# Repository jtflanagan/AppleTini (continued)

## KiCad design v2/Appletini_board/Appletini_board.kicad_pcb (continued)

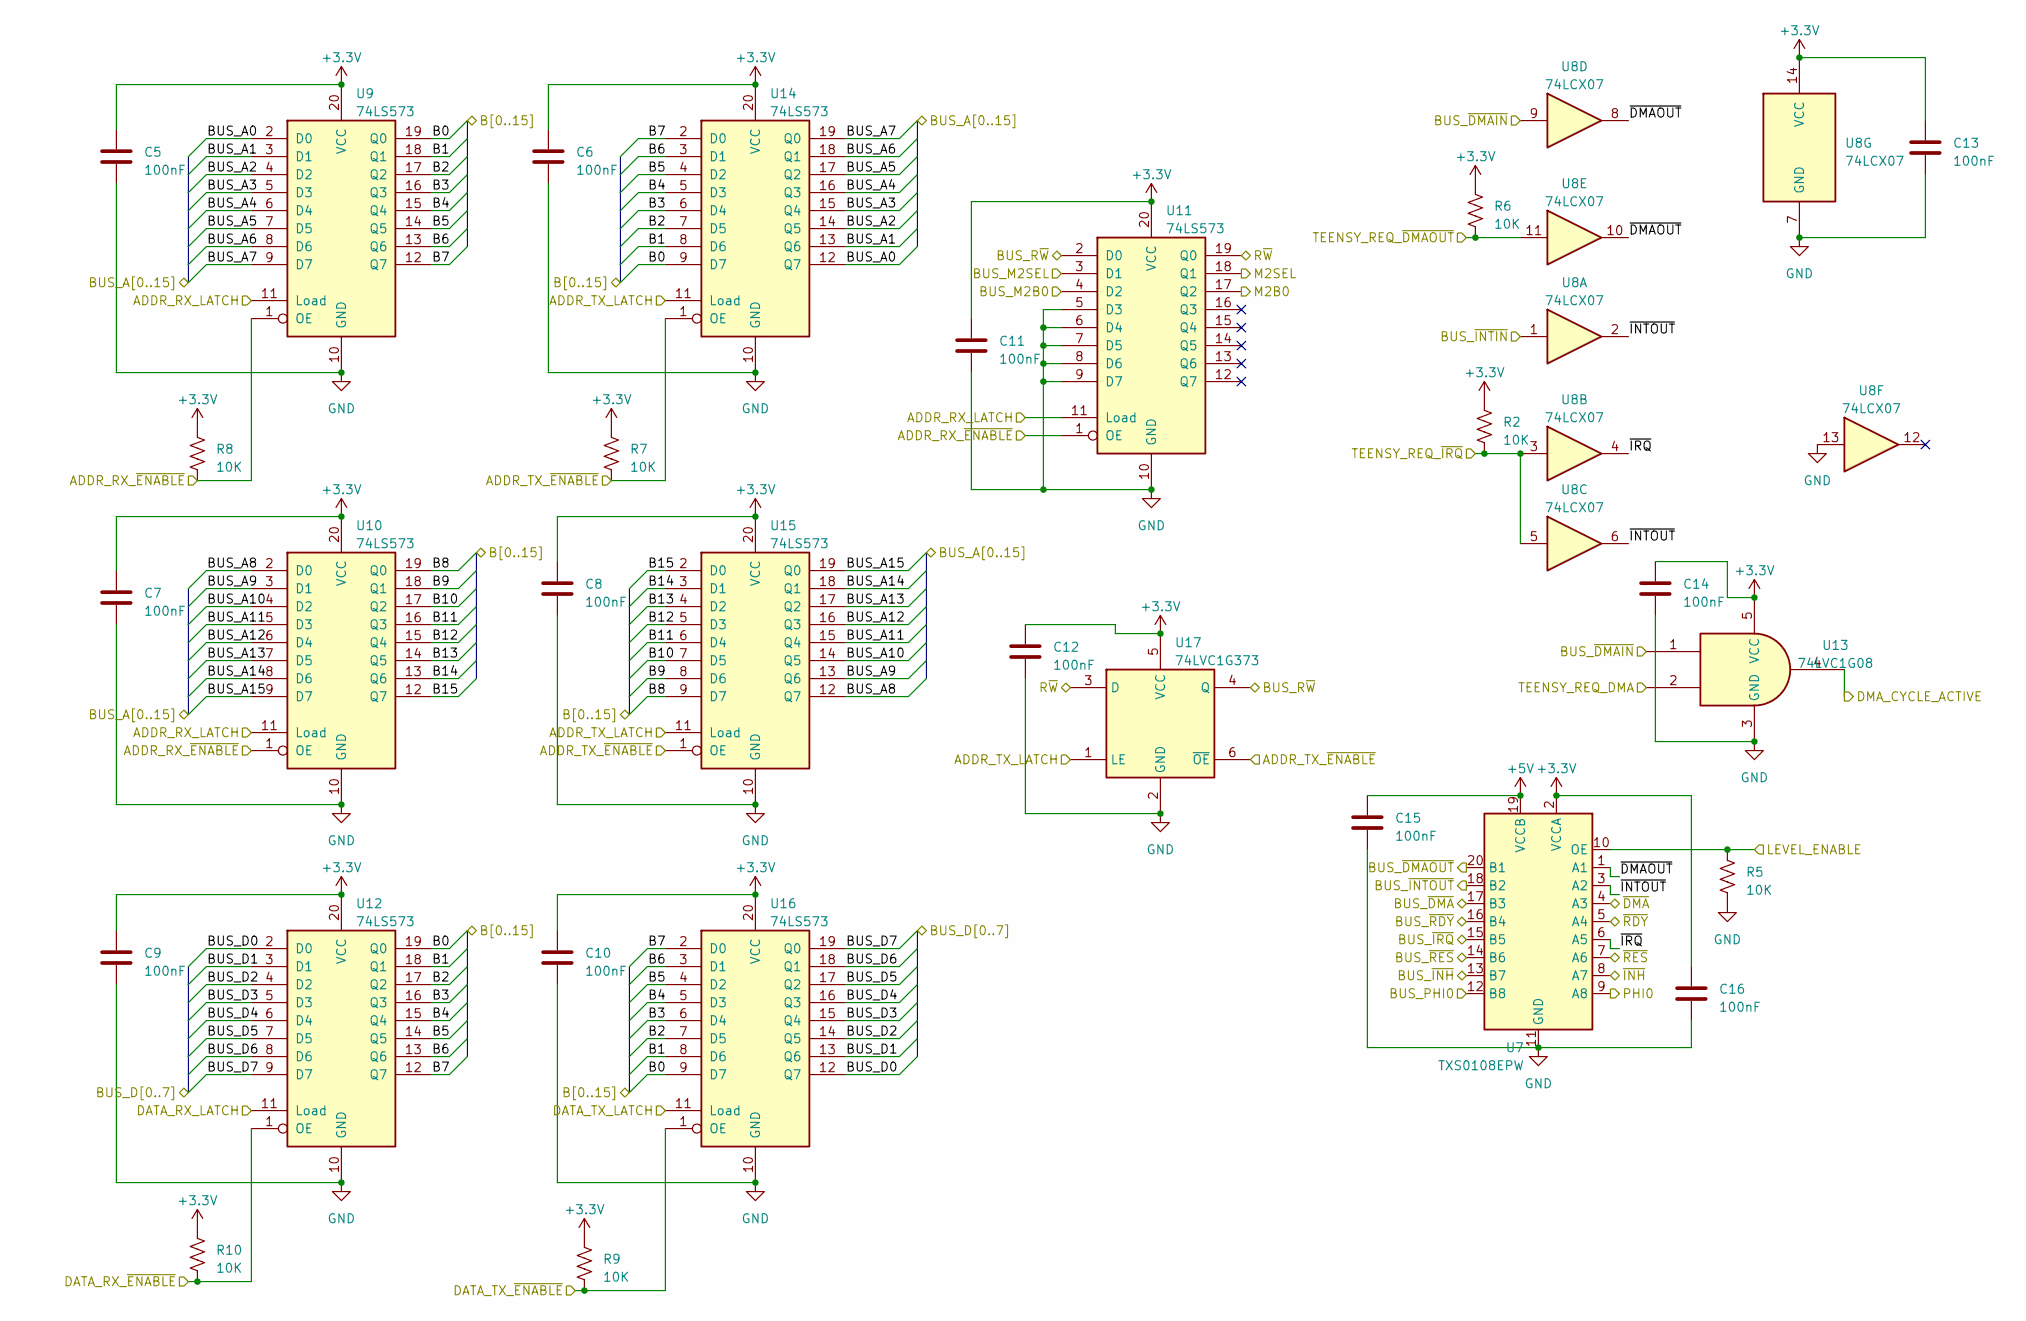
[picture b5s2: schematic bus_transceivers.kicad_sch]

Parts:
C5, C6, C7, C8, C9, C10, C11, C12: 100nF; C_1206_3216Metric
C13, C14, C15, C16: 100nF; C_1206_3216Metric; LCSC C24497
R2, R6, R7, R8, R9, R10: 10K; R_0402_1005Metric; LCSC C2991755
R5: 10K; R_0402_1005Metric
U7: TXS0108EPW; TSSOP-20_4.4x6.5mm_P0.65mm; LCSC C17206
U8: 74LCX07; TSSOP-14_4.4x5mm_P0.65mm; LCSC C7809
U9: 74LS573; TSSOP-20_4.4x6.5mm_P0.65mm; LCSC C113280
U10, U11, U12, U14, U15, U16: 74LS573; TSSOP-20_4.4x6.5mm_P0.65mm
U13: 74LVC1G08; SOT-23-5; LCSC C7666
U17: 74LVC1G373; SOT-23-6; LCSC C128413

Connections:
+3.3V: C5.1, C6.1, C7.1, C8.1, C9.1, C10.1, C11.1, C12.1, C13.1, C14.1, C16.1, R2.1, R6.1, R7.1, R8.1, R9.1, R10.1, U7.2 (VCCA), U8.14 (VCC), U9.20 (VCC), U10.20 (VCC), U11.20 (VCC), U12.20 (VCC), U13.5 (VCC), U14.20 (VCC), U15.20 (VCC), U16.20 (VCC), U17.5 (VCC); also elsewhere on the board
+5V: C15.1, U7.19 (VCCB); also elsewhere on the board
/ADDR_RX_LATCH: U9.11 (Load), U10.11 (Load), U11.11 (Load); also elsewhere on the board
/ADDR_RX_~ENABLE: R8.2, U9.1 (OE), U10.1 (OE), U11.1 (OE); also elsewhere on the board
/ADDR_TX_LATCH: U14.11 (Load), U15.11 (Load), U17.1 (LE); also elsewhere on the board
/ADDR_TX_~ENABLE: R7.2, U14.1 (OE), U15.1 (OE), U17.6 (~OE); also elsewhere on the board
/B0: U9.19 (Q0), U12.19 (Q0), U14.9 (D7), U16.9 (D7); also elsewhere on the board
/B1: U9.18 (Q1), U12.18 (Q1), U14.8 (D6), U16.8 (D6); also elsewhere on the board
/B2: U9.17 (Q2), U12.17 (Q2), U14.7 (D5), U16.7 (D5); also elsewhere on the board
/B3: U9.16 (Q3), U12.16 (Q3), U14.6 (D4), U16.6 (D4); also elsewhere on the board
/B4: U9.15 (Q4), U12.15 (Q4), U14.5 (D3), U16.5 (D3); also elsewhere on the board
/B5: U9.14 (Q5), U12.14 (Q5), U14.4 (D2), U16.4 (D2); also elsewhere on the board
/B6: U9.13 (Q6), U12.13 (Q6), U14.3 (D1), U16.3 (D1); also elsewhere on the board
/B7: U9.12 (Q7), U12.12 (Q7), U14.2 (D0), U16.2 (D0); also elsewhere on the board
/B8: U10.19 (Q0), U15.9 (D7); also elsewhere on the board
/B9: U10.18 (Q1), U15.8 (D6); also elsewhere on the board
/B10: U10.17 (Q2), U15.7 (D5); also elsewhere on the board
/B11: U10.16 (Q3), U15.6 (D4); also elsewhere on the board
/B12: U10.15 (Q4), U15.5 (D3); also elsewhere on the board
/B13: U10.14 (Q5), U15.4 (D2); also elsewhere on the board
/B14: U10.13 (Q6), U15.3 (D1); also elsewhere on the board
/B15: U10.12 (Q7), U15.2 (D0); also elsewhere on the board
/BUS_A0: U9.2 (D0), U14.12 (Q7); also elsewhere on the board
/BUS_A1: U9.3 (D1), U14.13 (Q6); also elsewhere on the board
/BUS_A2: U9.4 (D2), U14.14 (Q5); also elsewhere on the board
/BUS_A3: U9.5 (D3), U14.15 (Q4); also elsewhere on the board
/BUS_A4: U9.6 (D4), U14.16 (Q3); also elsewhere on the board
/BUS_A5: U9.7 (D5), U14.17 (Q2); also elsewhere on the board
/BUS_A6: U9.8 (D6), U14.18 (Q1); also elsewhere on the board
/BUS_A7: U9.9 (D7), U14.19 (Q0); also elsewhere on the board
/BUS_A8: U10.2 (D0), U15.12 (Q7); also elsewhere on the board
/BUS_A9: U10.3 (D1), U15.13 (Q6); also elsewhere on the board
/BUS_A10: U10.4 (D2), U15.14 (Q5); also elsewhere on the board
/BUS_A11: U10.5 (D3), U15.15 (Q4); also elsewhere on the board
/BUS_A12: U10.6 (D4), U15.16 (Q3); also elsewhere on the board
/BUS_A13: U10.7 (D5), U15.17 (Q2); also elsewhere on the board
/BUS_A14: U10.8 (D6), U15.18 (Q1); also elsewhere on the board
/BUS_A15: U10.9 (D7), U15.19 (Q0); also elsewhere on the board
/BUS_D0: U12.2 (D0), U16.12 (Q7); also elsewhere on the board
/BUS_D1: U12.3 (D1), U16.13 (Q6); also elsewhere on the board
/BUS_D2: U12.4 (D2), U16.14 (Q5); also elsewhere on the board
/BUS_D3: U12.5 (D3), U16.15 (Q4); also elsewhere on the board
/BUS_D4: U12.6 (D4), U16.16 (Q3); also elsewhere on the board
/BUS_D5: U12.7 (D5), U16.17 (Q2); also elsewhere on the board
/BUS_D6: U12.8 (D6), U16.18 (Q1); also elsewhere on the board
/BUS_D7: U12.9 (D7), U16.19 (Q0); also elsewhere on the board
/BUS_M2B0: U11.4 (D2); also elsewhere on the board
/BUS_M2SEL: U11.3 (D1); also elsewhere on the board
/BUS_PHI0: U7.12 (B8); also elsewhere on the board
/BUS_R~W: U11.2 (D0), U17.4 (Q); also elsewhere on the board
/BUS_~DMAIN: U8.9, U13.1; also elsewhere on the board
/BUS_~DMAOUT: U7.20 (B1); also elsewhere on the board
/BUS_~DMA: U7.17 (B3); also elsewhere on the board
/BUS_~INH: U7.13 (B7); also elsewhere on the board
/BUS_~INTIN: U8.1; also elsewhere on the board
/BUS_~INTOUT: U7.18 (B2); also elsewhere on the board
/BUS_~IRQ: U7.15 (B5); also elsewhere on the board
/BUS_~RDY: U7.16 (B4); also elsewhere on the board
/BUS_~RES: U7.14 (B6); also elsewhere on the board
/Bus transceivers/~DMAOUT: U7.1 (A1), U8.8, U8.10
/Bus transceivers/~INTOUT: U7.3 (A2), U8.2, U8.6
/Bus transceivers/~IRQ: U7.6 (A5), U8.4
/DATA_RX_LATCH: U12.11 (Load); also elsewhere on the board
/DATA_RX_~ENABLE: R10.2, U12.1 (OE); also elsewhere on the board
/DATA_TX_LATCH: U16.11 (Load); also elsewhere on the board
/DATA_TX_~ENABLE: R9.2, U16.1 (OE); also elsewhere on the board
/DMA_CYCLE_ACTIVE: U13.4; also elsewhere on the board
/LEVEL_ENABLE: R5.1, U7.10 (OE); also elsewhere on the board
/M2B0: U11.17 (Q2); also elsewhere on the board
/M2SEL: U11.18 (Q1); also elsewhere on the board
/PHI0: U7.9 (A8); also elsewhere on the board
/R~W: U11.19 (Q0), U17.3 (D); also elsewhere on the board
/TEENSY_REQ_DMA: U13.2; also elsewhere on the board
/TEENSY_REQ_~DMAOUT: R6.2, U8.11; also elsewhere on the board
/TEENSY_REQ_~IRQ: R2.2, U8.3, U8.5; also elsewhere on the board
/~DMA: U7.4 (A3); also elsewhere on the board
/~INH: U7.8 (A7); also elsewhere on the board
/~RDY: U7.5 (A4); also elsewhere on the board
/~RES: U7.7 (A6); also elsewhere on the board
GND: C5.2, C6.2, C7.2, C8.2, C9.2, C10.2, C11.2, C12.2, C13.2, C14.2, C15.2, C16.2, R5.2, U7.11 (GND), U8.7 (GND), U8.13, U9.10 (GND), U10.10 (GND), U11.5 (D3), U11.6 (D4), U11.7 (D5), U11.8 (D6), U11.9 (D7), U11.10 (GND), U12.10 (GND), U13.3 (GND), U14.10 (GND), U15.10 (GND), U16.10 (GND), U17.2 (GND); also elsewhere on the board

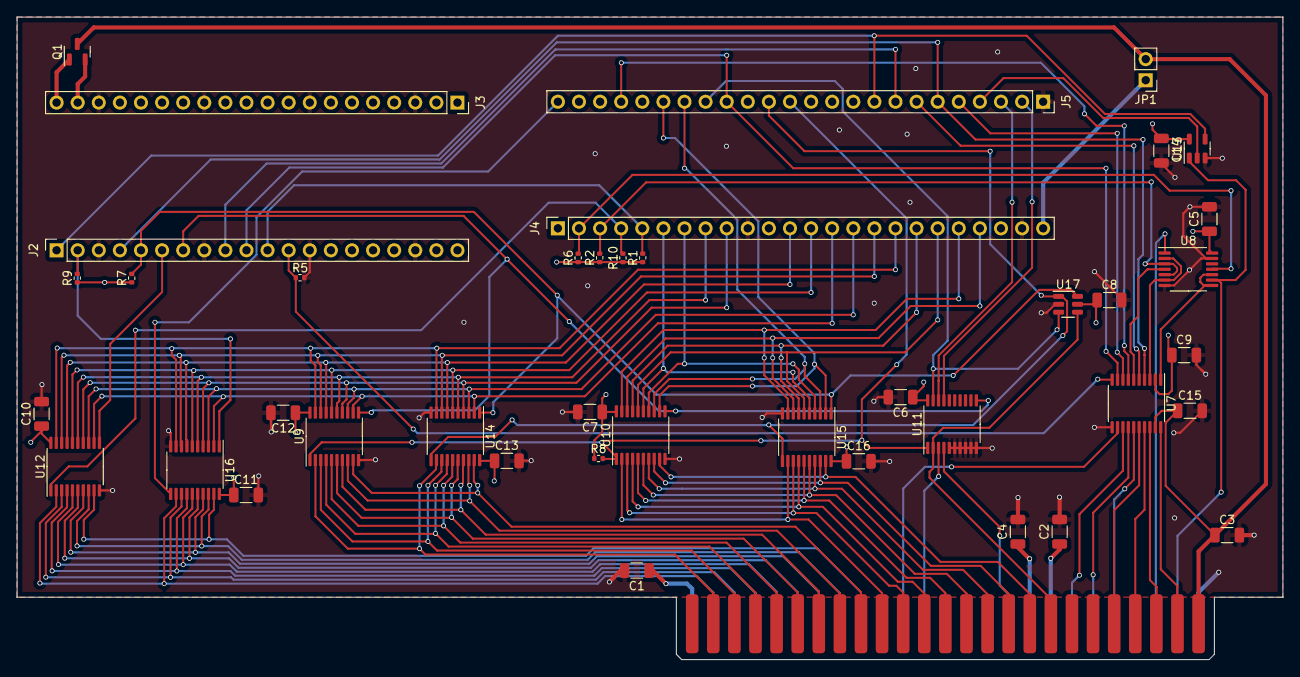
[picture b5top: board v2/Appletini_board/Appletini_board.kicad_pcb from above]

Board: 4 copper layers, 152.4 x 77.4 mm, 42 parts (0 on the bottom side), 88 nets.

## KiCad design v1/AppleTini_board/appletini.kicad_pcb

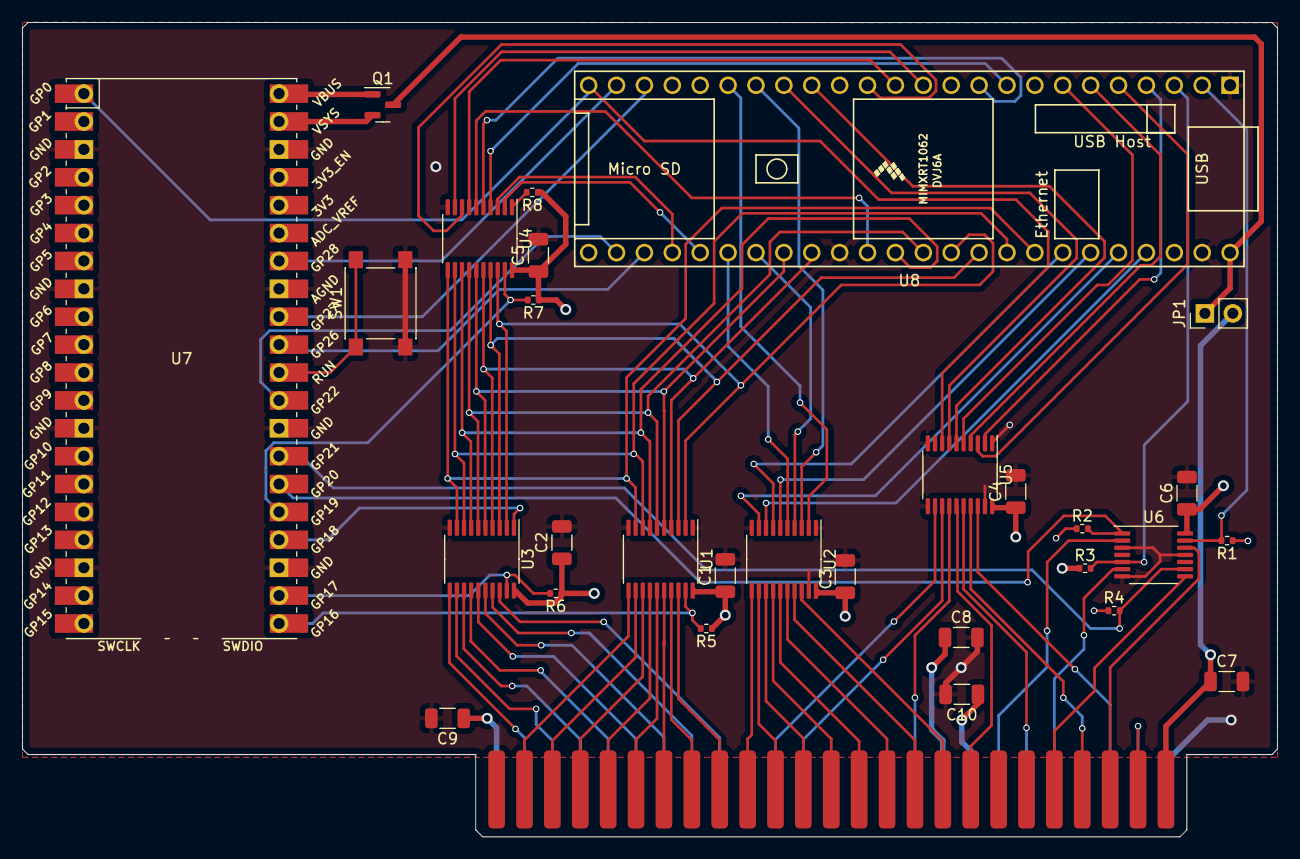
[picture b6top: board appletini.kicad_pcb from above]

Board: 4 copper layers, 114.3 x 74.2 mm, 30 parts (0 on the bottom side), 90 nets.

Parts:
C1, C2, C3, C4, C5, C6, C7, C8, C9, C10: 0.1uF; C_1206_3216Metric
J1: Conn_02x25_Counter_Clockwise; AppleIIBus_Edge
JP1: Jumper_2_Open; PinHeader_1x02_P2.54mm_Vertical
Q1: DMG2305UX-7; SOT-23
R1, R2, R3, R4, R5, R6, R7, R8: 10K; R_0402_1005Metric
SW1: SW_Push; SW_Push_1P1T_NO_6x6mm_H9.5mm
U1, U2, U3, U4, U5: 74LS245; TSSOP-20_4.4x6.5mm_P0.65mm
U6: 74LS07; TSSOP-14_4.4x5mm_P0.65mm
U7: Pico; RPi_Pico_SMD_TH
U8: Teensy4.1; Teensy41

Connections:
+3.3V: C1.1, C2.1, C3.1, C4.1, C5.1, C6.1, R1.1, R2.1, R3.1, R4.1, R5.1, R6.1, R7.1, R8.1, U1.20 (VCC), U2.20 (VCC), U3.20 (VCC), U4.20 (VCC), U5.20 (VCC), U6.14 (VCC), U8.46 (3V3)
+5V: C7.1, J1.25, JP1.2 (B)
+12V: C9.1, J1.50
-5V: C8.1, J1.34
-12V: C10.1, J1.33
/ALO_EN: R5.2, U1.19 (CE), U7.21 (GPIO16)
/BUS_A0: J1.2, U1.11 (B7)
/BUS_A1: J1.3, U1.12 (B6)
/BUS_A2: J1.4, U1.13 (B5)
/BUS_A3: J1.5, U1.14 (B4)
/BUS_A4: J1.6, U1.15 (B3)
/BUS_A5: J1.7, U1.16 (B2)
/BUS_A6: J1.8, U1.17 (B1)
/BUS_A7: J1.9, U1.18 (B0)
/BUS_A8: J1.10, U2.11 (B7)
/BUS_A9: J1.11, U2.12 (B6)
/BUS_A10: J1.12, U2.13 (B5)
/BUS_A11: J1.13, U2.14 (B4)
/BUS_A12: J1.14, U2.15 (B3)
/BUS_A13: J1.15, U2.16 (B2)
/BUS_A14: J1.16, U2.17 (B1)
/BUS_A15: J1.17, U2.18 (B0)
/BUS_D0: J1.49, U3.11 (B7)
/BUS_D1: J1.48, U3.12 (B6)
/BUS_D2: J1.47, U3.13 (B5)
/BUS_D3: J1.46, U3.14 (B4)
/BUS_D4: J1.45, U3.15 (B3)
/BUS_D5: J1.44, U3.16 (B2)
/BUS_D6: J1.43, U3.17 (B1)
/BUS_D7: J1.42, U3.18 (B0)
/BUS_DMA: J1.22, U5.17 (B1)
/BUS_DMAPASS: J1.24, J1.27
/BUS_INH: J1.32, U6.2
/BUS_INTIN: J1.28, U5.18 (B0)
/BUS_INTOUT: J1.23, U6.12
/BUS_IRQ: J1.30, U6.6
/BUS_M2B0: J1.35, U5.14 (B4)
/BUS_PHI0: J1.40, U5.12 (B6)
/BUS_RDY: J1.21, U6.8
/BUS_RES: J1.31, U5.16 (B2)
/BUS_RW: J1.18, U5.15 (B3)
/BUS_uSYNC: J1.39, U5.13 (B5)
/DMA: U5.3 (A1), U8.5 (3_LRCLK2)
/D_DIR: U3.1 (A->B), U7.24 (GPIO18)
/D_EN: R6.2, U3.19 (CE), U7.22 (GPIO17)
/INH: R2.2, U6.1, U7.26 (GPIO20)
/INH_REQ: U7.29 (GPIO22), U8.26 (34_RX8)
/INTIN: U5.2 (A0), U8.4 (2_OUT2)
/INTOUT: R1.2, U6.13, U8.2 (0_RX1_CRX2_CS1)
/IRQ: R3.2, U6.5, U8.3 (1_TX1_CTX2_MISO1)
/M2B0: U5.6 (A4), U8.16 (24_A10_TX6_SCL2)
/OUT_D_EN: R7.2, U4.19 (CE), U7.25 (GPIO19)
/OUT_D_REQ: U7.34 (GPIO28_ADC2), U8.23 (31_CTX3)
/PHI0: U5.8 (A6), U7.1 (GPIO0), U8.24 (32_OUT1B)
/RDY: R4.2, U6.9, U7.27 (GPIO21)
/RDY_REQ: U7.31 (GPIO26_ADC0), U8.27 (35_TX8)
/RES: U5.4 (A2), U8.6 (4_BCLK2)
/RW: U5.5 (A3), U8.7 (5_IN2)
/TEENSY_IRQ: U7.32 (GPIO27_ADC1), U8.22 (30_CRX3)
/Transceivers/AHI0: U2.9 (A7), U8.44 (22_A8_CTX1)
/Transceivers/AHI1: U2.8 (A6), U8.45 (23_A9_CRX1_MCLK1)
/Transceivers/AHI2: U2.7 (A5), U8.42 (20_A6_TX5_LRCLK1)
/Transceivers/AHI3: U2.6 (A4), U8.43 (21_A7_RX5_BCLK1)
/Transceivers/AHI4: U2.5 (A3), U8.30 (38_CS1_IN1)
/Transceivers/AHI5: U2.4 (A2), U8.31 (39_MISO1_OUT1A)
/Transceivers/AHI6: U2.3 (A1), U8.18 (26_A12_MOSI1)
/Transceivers/AHI7: U2.2 (A0), U8.19 (27_A13_SCK1)
/Transceivers/ALO_D0: U1.9 (A7), U3.9 (A7), U4.11 (B7), U8.41 (19_A5_SCL)
/Transceivers/ALO_D1: U1.8 (A6), U3.8 (A6), U4.12 (B6), U8.40 (18_A4_SDA)
/Transceivers/ALO_D2: U1.7 (A5), U3.7 (A5), U4.13 (B5), U8.36 (14_A0_TX3_SPDIF_OUT)
/Transceivers/ALO_D3: U1.6 (A4), U3.6 (A4), U4.14 (B4), U8.37 (15_A1_RX3_SPDIF_IN)
/Transceivers/ALO_D4: U1.5 (A3), U3.5 (A3), U4.15 (B3), U8.32 (40_A16)
/Transceivers/ALO_D5: U1.4 (A2), U3.4 (A2), U4.16 (B2), U8.33 (41_A17)
/Transceivers/ALO_D6: U1.3 (A1), U3.3 (A1), U4.17 (B1), U8.39 (17_A3_TX4_SDA1)
/Transceivers/ALO_D7: U1.2 (A0), U3.2 (A0), U4.18 (B0), U8.38 (16_A2_RX4_SCL1)
/Transceivers/OUT_D0: U4.9 (A7), U8.12 (10_CS_MQSR)
/Transceivers/OUT_D1: U4.8 (A6), U8.14 (12_MISO_MQSL)
/Transceivers/OUT_D2: U4.7 (A5), U8.13 (11_MOSI_CTX1)
/Transceivers/OUT_D3: U4.6 (A4), U8.35 (13_SCK_LED)
/Transceivers/OUT_D4: U4.5 (A3), U8.10 (8_TX2_IN1)
/Transceivers/OUT_D5: U4.4 (A2), U8.9 (7_RX2_OUT1A)
/Transceivers/OUT_D6: U4.3 (A1), U8.28 (36_CS)
/Transceivers/OUT_D7: U4.2 (A0), U8.29 (37_CS)
/VBUS: Q1.1 (G), U7.40 (VBUS)
/VIN: JP1.1 (A), Q1.3 (D), U8.48 (VIN)
/VSYS: Q1.2 (S), U7.39 (VSYS)
/uSYNC: U5.7 (A5), U8.17 (25_A11_RX6_SDA2)
GND: C1.2, C2.2, C3.2, C4.2, C5.2, C6.2, C7.2, C8.2, C9.2, C10.2, J1.26, SW1.2, U1.1 (A->B), U1.10 (GND), U2.1 (A->B), U2.10 (GND), U2.19 (CE), U3.10 (GND), U4.10 (GND), U5.1 (A->B), U5.10 (GND), U5.11 (B7), U5.19 (CE), U6.3, U6.7 (GND), U6.11, U7.3 (GND), U7.8 (GND), U7.13 (GND), U7.18 (GND), U7.23 (GND), U7.28 (GND), U7.33 (AGND), U7.38 (GND), U8.1 (GND), U8.34 (GND), U8.47 (GND)
unnamed: R8.2, U4.1 (A->B)
unnamed: SW1.1, U7.30 (RUN)

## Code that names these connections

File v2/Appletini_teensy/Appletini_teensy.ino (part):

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  bus_address = (addr_port6_pins & 0xffff0000) >> 16;
  // these are set to the offsets they will eventually get used as
  // for event publish, and used in boolean context otherwise
  bus_rw = (addr_port6_pins & (1 << 13)) ? (1 << 24) : 0;
  bus_m2sel = (addr_port6_pins & (1 << 2)) ? (1 << 25) : 0;
  bus_m2b0 = (addr_port6_pins & (1 << 3)) ? (1 << 26) : 0;
  bus_reset = (port9_pins & (1 << 31)) ? (1 << 27) : 0;

  // make whatever decision as to what to do on this bus cycle based on
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  pinMode(PIN_RW, INPUT);

  // M2SEL on IIgs, uSYNC on IIe.  Always an input.
  pinMode(PIN_M2SEL, INPUT);
  // M2B0 on IIgs, not used on IIe. Always an input.
  pinMode(PIN_M2B0, INPUT);

  // ADDR_RX_ENABLE
  // DATA_RX_ENABLE
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  // the bus interrupt can snap the address lines immediately.
  // other bus actions will deassert ADDR_RX_ENABLE but we return
  // to a default state of ADDR_RX_ENABLE afterward.
  init_output_pin(PIN_ADDR_RX_ENABLE, LOW);
  init_output_pin(PIN_DATA_RX_ENABLE, HIGH);

  // ADDR_TX_LATCH
  // DATA_TX_LATCH
  // pins to tell the TX latches to retain their latched values.
  // Always outputs, init low
  init_output_pin(PIN_ADDR_TX_LATCH, LOW);
  init_output_pin(PIN_DATA_TX_LATCH, LOW);

  // TEENSY_EMIT_DATA
  // pin to tell Pico that the current bus cycle should emit the latched data byte.
  // always outputs, init high
  init_output_pin(PIN_TEENSY_EMIT_DATA, HIGH);

  // TEENSY_REQ_DMAOUT
  // pin to pre-request DMA.  This should be asserted the cycle before beginning DMA request.
  // always outputs, init high
  init_output_pin(PIN_TEENSY_REQ_DMAOUT, HIGH);

  // DMA_CYCLE_ACTIVE
  // pin indicating whether the current bus cycle is a DMA cycle under Teensy control.
  // always input
  pinMode(PIN_DMA_CYCLE_ACTIVE, INPUT);

  // TEENSY_REQ_IRQ
  // pin to request apple IRQ assert.
  // always output, init high
  init_output_pin(PIN_TEENSY_REQ_IRQ, HIGH);

  // INH
  // pin to instruct Apple that the current cycle is inhibiting the motherboard memory.
  // defaults to input (pin floating high-impedance), and is asserted by setting the pin to output low
  pinMode(PIN_INH, INPUT);

  // DMA
  // never actively controlled by the Teensy, but allows the Teensy to see when DMA is occurring
  // other than when it is doing the DMA itself.
  // set to input (pin floating high-impedance).
  pinMode(PIN_DMA, INPUT);

  // RDY
  // pin to instruct Apple to stall this cycle's bus read event.
  // defaults to input (pin floating high-impedance), and is asserted by setting the pin to output low
  pinMode(PIN_RDY, INPUT);

  // RES
  // pin to force an Apple reboot.
  // defaults to input (pin floating high-impedance), and is asserted by setting the pin to output low
  pinMode(PIN_RES, INPUT);

  // TEENSY_IRQ, the pin we get address-phase interrupts from the Pico.  Always an input.
  pinMode(PIN_TEENSY_IRQ, INPUT);



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
  cli();
  // let the lib code in attachInterrupt do its config details
  attachInterrupt(digitalPinToInterrupt(PIN_TEENSY_IRQ), bus_handler, FALLING);

  // override the vector for GPIO directly to our handler to skip dispatching
  attachInterruptVector(IRQ_GPIO6789, &bus_handler);
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
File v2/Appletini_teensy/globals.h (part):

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// rw pin, GPIO6.13
#define PIN_RW 25

// M2SEL/uSYNC, GPIO6.3
#define PIN_M2SEL 0
// M2B0, GPIO6.2
#define PIN_M2B0 1

// TEENSY_IRQ, GPIO7.10
// this is the interrupt pin from the Pico to tell us to snap the address and data latches
#define PIN_TEENSY_IRQ 6

// ADDR_RX_ENABLE, GPIO7.2
// this is the output enable for the ADDR RX latches.
// this enables the latched address onto B0-B15,
// as well as enabling the latched values for RW, M2SEL, and M2B0.
#define PIN_ADDR_RX_ENABLE 11
// DATA_RX_ENABLE, GPIO7.18
// this is the output enable for the DATA RXlatch.
// this puts the latched data byte onto B0-B7.
#define PIN_DATA_RX_ENABLE 36

// ADDR_TX_LATCH, GPIO7.1
// this is the latch enable for the ADDR TX latches.
// when this line transitions High->Low, the ADDR TX latches store
// the current values of B0-B15 and RW
#define PIN_ADDR_TX_LATCH 12
// DATA_TX_LATCH, GPIO7.12
// this is the latch enable for the DATA TX latch.
// when this line transitions High->Low, the DATA TX latch stores
// the current values of B0-B7
#define PIN_DATA_TX_LATCH 32

// TEENSY_EMIT_DATA, GPIO7.19
// This line, active-low, is asserted when the Teensy is intending
// to emit the data byte for the current bus cycle.  The desired byte
// should be stored on the DATA TX latch, and this line asserted low.
// At the next interrupt, the line should be deasserted high.
#define PIN_TEENSY_EMIT_DATA 37

// TEENSY_REQ_DMAOUT, GPIO7.29
// This line, active low, should be asserted when the Teensy intends to
// start performing DMA.  This should be done one cycle in advance before
// actual DMA is requested, so that lower priority cards get advance notice
// that they need to get off the bus.
// this should be deasserted when the desired DMA is complete.
#define PIN_TEENSY_REQ_DMAOUT 34

// TEENSY_REQ_DMA, GPIO9.4
// This line, active high, should be asserted when the Teensy intends to
// start performing DMA.  This should be done the following cycle after asserting
// TEENSY_REQ_DMAOUT.  This does not imply that DMA will be permitted yet!
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// priority cards are no longer claiming DMA access.  If the DMA_CYCLE_ACTIVE
// line is asserted when the TEENSY_IRQ interrupt occurs, then the current cycle
// should perform the DMA request.
#define PIN_TEENSY_REQ_DMA 2

// DMA_CYCLE_ACTIVE, GPIO7.17
// this line, active high, is asserted when the current bus cycle is allowed
// to fulfill the current DMA request.  The Teensy should sample this line during
// the TEENSY_IRQ interrupt to know if it can do its desired DMA.
#define PIN_DMA_CYCLE_ACTIVE 7

// TEENSY_REQ_IRQ, GPIO7.28
// This line, active low, should be asserted when the teensy wants to request
// an IRQ on the Apple.  There are no particular timing requirements for this line,
// but neither are there requirements for when the Apple interrupt process gets
// around to calling the Teensy's specific handler (or handlers).  Once the request
// is serviced, the line should be deasserted.
#define PIN_TEENSY_REQ_IRQ 35

// INH, GPIO9.5
// This line, active low, should be asserted in the TEENSY_IRQ interrupt when
// the current address read should be inhibited from motherboard memory
// and served by the Teensy instead (by asserting TEENSY_EMIT_DATA as well).
// Otherwise the line should be set as INPUT and left high impedance.
#define PIN_INH 3

// DMA, GPIO9.6
// this line, active low, should NOT be asserted by the Teensy, but only
// used as an advisement that the current bus cycle is a DMA cycle-
// which could be the Teensy's own requested cycle, or another card's.
// Otherwise the line should be set as INPUT and left high impedance.
#define PIN_DMA 4

// RDY, GPIO9.8
// this line, active low, should be asserted in the TEENSY_IRQ interrupt when
// the current address read is intended to be stalled.  It should NOT be
// asserted when the RW line indicates that the current cycle is a write,
// because the 6502 does not respect the line on write cycles.
// Otherwise the line should be set as INPUT and left high impedance.
#define PIN_RDY 5

// RES, GPIO9.31
// this line, active low, should be asserted when the Teensy is invoking
// a reset on the Apple.
// Otherwise the line should be set as INPUT and left high impedance.
#define PIN_RES 29

#define PREBOOT_CARD_IMAGE_V1 { \
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
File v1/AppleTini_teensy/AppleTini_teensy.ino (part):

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 When AddressReady signals, the ISR reads the 16 bits of Apple bus address,
 and the RW bit, and saves them for the DataReady phase.  In addition, if
 the RW flag indicates a read, it examines the address and decides whether
 to emit the byte read, or not.  It sets the active-low OUT_D_REQ pin
 appropriately, and puts the emitted byte onto the 8 data-out pins.

 When DataReady signals, the ISR reads the 8 bits of Apple bus data (which
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// the two clumps of 4 at 0-3 and 16-19 are the
// low and high half of the data byte.
#define DATA_OUT_MASK 0x000f000f
// OUT_D_REQ is on GPIO8, bit 22
#define OUT_D_REQ_MASK 0x00400000
// RDY_REQ is on GPIO7, bit 28
#define RDY_REQ_MASK 0x10000000
// INH_REQ is on GPIO7, bit 29
#define INH_REQ_MASK 0x20000000
// IRQ is on GPIO6, bit 02
#define IRQ_MASK 0x00000004
// INTOUT is on GPIO6, bit 03
#define INTOUT_MASK 0x00000008

FASTRUN static inline void check_soft_switches(uint8_t data) {
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}

FASTRUN static inline void do_address_phase(uint32_t gpio6_pins, uint32_t gpio9_pins) {
  // first disable OUT_D_REQ pin (set high, as it is active-low)
  GPIO8_DR_SET = OUT_D_REQ_MASK;

  // we arranged for the address pins to be the contiguous set of bits 16-31
  bus_address = (gpio6_pins >> 16) & 0xffff;
  // toggle io_strobe if needed
  bus_rw = (gpio9_pins >> 8) & 0x01;
  bus_m2b0 = (gpio6_pins >> 12) & 0x01;
  bus_m2sel = (gpio6_pins >> 13) & 0x01;
  // // forward INTIN to INTOUT
  // // TODO- if we ever do our own interrupt, we would need to flag it
  // // Thinking more about this, we should be doing this in hardware, auto
  // // forwarding instantly by default and only pulling it down if we decide
  // // it's safe because INTIN is high, and we want to do an interrupt
  // uint32_t intin = (gpio9_pins >> 4) & 0x01;
  // if (intin) {
  //   GPIO6_DR_SET = INTOUT_MASK;
  // } else {
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
FASTRUN void bus_handler() {
  // snap the pins immediately
  uint32_t port6_pins = GPIO6_PSR;  // address/data, and M2B0/uSYNC
  uint32_t port7_pins = GPIO7_PSR;  // PHI0 is on GPIO7 12
  uint32_t port9_pins = GPIO9_PSR;
  // clear interrupts.  We are doing it slightly faster than the
  // stock interrupt code, because we know we are the only gpio
  // interrupt running, and we are only on GPIO8 23 (TEENSY_IRQ).
  volatile uint32_t* drp = &GPIO8_DR;
  uint32_t interrupt_status = drp[ISR_INDEX] & drp[IMR_INDEX];
  drp[ISR_INDEX] = interrupt_status;  // this clears the interrupt

  // PHI0 (pin 32, GPIO7 bit 12)
  if (port7_pins & CORE_PIN32_BITMASK) {
    //Serial.println("data");
    do_data_phase(port6_pins, port9_pins);
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
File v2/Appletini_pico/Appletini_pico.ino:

#include <hardware/pio.h>
#include "bus_controller.pio.h"

#include "hardware/pll.h"
#include "hardware/clocks.h"

void set_sys_clock_pll(uint32_t vco_freq, uint post_div1, uint post_div2) {
  if (!running_on_fpga()) {
    clock_configure(clk_sys,
                    CLOCKS_CLK_SYS_CTRL_SRC_VALUE_CLKSRC_CLK_SYS_AUX,
                    CLOCKS_CLK_SYS_CTRL_AUXSRC_VALUE_CLKSRC_PLL_USB,
                    48 * MHZ,
                    48 * MHZ);

    pll_init(pll_sys, 1, vco_freq, post_div1, post_div2);
    uint32_t freq = vco_freq / (post_div1 * post_div2);

    // Configure clocks
    // CLK_REF = XOSC (12MHz) / 1 = 12MHz
    clock_configure(clk_ref,
                    CLOCKS_CLK_REF_CTRL_SRC_VALUE_XOSC_CLKSRC,
                    0,  // No aux mux
                    12 * MHZ,
                    12 * MHZ);

    // CLK SYS = PLL SYS (125MHz) / 1 = 125MHz
    clock_configure(clk_sys,
                    CLOCKS_CLK_SYS_CTRL_SRC_VALUE_CLKSRC_CLK_SYS_AUX,
                    CLOCKS_CLK_SYS_CTRL_AUXSRC_VALUE_CLKSRC_PLL_SYS,
                    freq, freq);

    clock_configure(clk_peri,
                    0,  // Only AUX mux on ADC
                    CLOCKS_CLK_PERI_CTRL_AUXSRC_VALUE_CLKSRC_PLL_USB,
                    48 * MHZ,
                    48 * MHZ);
  }
}
bool check_sys_clock_khz(uint32_t freq_khz, uint *vco_out, uint *postdiv1_out, uint *postdiv_out) {
  uint crystal_freq_khz = clock_get_hz(clk_ref) / 1000;
  for (uint fbdiv = 320; fbdiv >= 16; fbdiv--) {
    uint vco = fbdiv * crystal_freq_khz;
    if (vco < 400000 || vco > 1600000) continue;
    for (uint postdiv1 = 7; postdiv1 >= 1; postdiv1--) {
      for (uint postdiv2 = postdiv1; postdiv2 >= 1; postdiv2--) {
        uint out = vco / (postdiv1 * postdiv2);
        if (out == freq_khz && !(vco % (postdiv1 * postdiv2))) {
          *vco_out = vco * 1000;
          *postdiv1_out = postdiv1;
          *postdiv_out = postdiv2;
          return true;
        }
      }
    }
  }
  return false;
}
static inline bool set_sys_clock_khz(uint32_t freq_khz, bool required) {
  uint vco, postdiv1, postdiv2;
  if (check_sys_clock_khz(freq_khz, &vco, &postdiv1, &postdiv2)) {
    set_sys_clock_pll(vco, postdiv1, postdiv2);
    return true;
  } else if (required) {
    panic("System clock of %u kHz cannot be exactly achieved", freq_khz);
  }
  return false;
}

enum {
  TEENSY_IRQ_GEN_SM = 0,
  ADDR_LOOP_SM = 1,
  DATA_LOOP_SM = 2,
};

#define BUS_PIO pio0
#define BUS_PIN_PHI0 7
#define BUS_PIN_IRQ_GEN_BASE 4
#define BUS_PIN_ADDR_BASE 2
#define BUS_PIN_DATA_BASE 1
#define BUS_PIN_DMA_CYCLE_ACTIVE 0
#define BUS_PIN_TEENSY_EMIT_DATA 8
#define BUS_PIN_LEVEL_ENABLE 9

static void teensy_irq_gen_setup(PIO pio, uint sm) {
  uint program_offset = pio_add_program(pio, &teensy_irq_gen_program);
  pio_sm_claim(pio, sm);
  pio_sm_config c = teensy_irq_gen_program_get_default_config(program_offset);
  // no jump pin
  // map the SET pin group to the control signals
  sm_config_set_set_pins(&c, BUS_PIN_IRQ_GEN_BASE, 3);
  pio_sm_init(pio, sm, program_offset, &c);
  // set outbound pins (TEENSY_IRQ, ADDR_RX_LATCH, DATA_RX_LATCH) initially high
  pio_sm_set_pins_with_mask(pio, sm,
    ((uint32_t)0x7 << BUS_PIN_IRQ_GEN_BASE),
    ((uint32_t)0x7 << BUS_PIN_IRQ_GEN_BASE));
  // set outbound pins pointing outbound, leaving PHI0 pointing inbound
  pio_sm_set_pindirs_with_mask(pio, sm, 
    ((uint32_t)0x7 << BUS_PIN_IRQ_GEN_BASE),
    ((uint32_t)0x1 << BUS_PIN_PHI0) | ((uint32_t)0x7 << BUS_PIN_IRQ_GEN_BASE));
  // configure PHI0
  pio_gpio_init(pio, BUS_PIN_PHI0);
  // disable internal pulls on PHI0
  gpio_set_pulls(BUS_PIN_PHI0, false, false);
  // configure and disable internal pulls on control pins as well (they have external pulls where needed)
  for (int i = 0; i < 3; ++i) {
    pio_gpio_init(pio, BUS_PIN_IRQ_GEN_BASE + i);
    gpio_set_pulls(BUS_PIN_IRQ_GEN_BASE + i, false, false);
  }
}

static void addr_loop_setup(PIO pio, uint sm) {
  uint program_offset = pio_add_program(pio, &addr_loop_program);
  pio_sm_claim(pio, sm);
  pio_sm_config c = addr_loop_program_get_default_config(program_offset);
  // jump pin is DMA_CYCLE_ACTIVE
  sm_config_set_jmp_pin(&c, BUS_PIN_DMA_CYCLE_ACTIVE);
  // map the SET pin group to the addr control group
  sm_config_set_set_pins(&c, BUS_PIN_ADDR_BASE, 2);
  pio_sm_init(pio, sm, program_offset, &c);
  // set outbound values for pins.  ADDR_TX_ENABLE is initially high,
  // DMA is initially low
  pio_sm_set_pins_with_mask(pio, sm,
    ((uint32_t)0x1 << BUS_PIN_ADDR_BASE),
    ((uint32_t)0x3 << BUS_PIN_ADDR_BASE));
  // set pindir to INPUT for DMA and OUTPUT for ADDR_TX_ENABLE, and inputs for PHI0 and DMA_CYCLE_ACTIVE
  pio_sm_set_pindirs_with_mask(pio, sm,
    ((uint32_t)0x1 << BUS_PIN_ADDR_BASE),
    ((uint32_t)0x3 << BUS_PIN_ADDR_BASE) | ((uint32_t)0x1 << BUS_PIN_PHI0) | ((uint32_t)0x1 << BUS_PIN_DMA_CYCLE_ACTIVE));
  // PHI0 already configured in first state machine, don't reconfigure
  // configure DMA_CYCLE_ACTIVE
  pio_gpio_init(pio, BUS_PIN_DMA_CYCLE_ACTIVE);
  // disable internal pulls on DMA_CYCLE_ACTIVE
  gpio_set_pulls(BUS_PIN_DMA_CYCLE_ACTIVE, false, false);
  // configure and disable internal pulls on control pins as well (they have external pulls where needed)
  for (int i = 0; i < 2; ++i) {
    pio_gpio_init(pio, BUS_PIN_ADDR_BASE + i);
    gpio_set_pulls(BUS_PIN_ADDR_BASE + i, false, false);
  }
}

static void data_loop_setup(PIO pio, uint sm) {
  uint program_offset = pio_add_program(pio, &data_loop_program);
  pio_sm_claim(pio, sm);
  pio_sm_config c = data_loop_program_get_default_config(program_offset);
  // jump pin is TEENSY_EMIT_DATA
  sm_config_set_jmp_pin(&c, BUS_PIN_TEENSY_EMIT_DATA);
  // map the SET pin group to the data control group
  sm_config_set_set_pins(&c, BUS_PIN_DATA_BASE, 1);
  pio_sm_init(pio, sm, program_offset, &c);
  // set outbound values for pins.  Only one pin really,
  // DATA_TX_ENABLE is initially high
  pio_sm_set_pins_with_mask(pio, sm,
    ((uint32_t)0x01 << BUS_PIN_DATA_BASE),
    ((uint32_t)0x01 << BUS_PIN_DATA_BASE));
  // set pindir to OUTPUT for ADDR_TX_ENABLE, and inputs for PHI0 and TEENSY_EMIT_DATA
  pio_sm_set_pindirs_with_mask(pio, sm,
    ((uint32_t)0x1 << BUS_PIN_DATA_BASE),
    ((uint32_t)0x1 << BUS_PIN_DATA_BASE) | ((uint32_t)0x1 << BUS_PIN_PHI0) | ((uint32_t)0x1 << BUS_PIN_TEENSY_EMIT_DATA));
  // PHI0 already configured in first state machine, don't reconfigure
  // configure BUS_PIN_TEENSY_EMIT_DATA
  pio_gpio_init(pio, BUS_PIN_TEENSY_EMIT_DATA);
  // disable internal pulls on TEENSY_EMIT_DATA, it has its own external pull
  gpio_set_pulls(BUS_PIN_TEENSY_EMIT_DATA, false, false);
  // configure and disable internal pulls on control pins as well (they have external pulls where needed)
  // yes, there's only one for this SM, but I'm trying to treat them uniformly in the code so it gets a loop
  for (int i = 0; i < 1; ++i) {
    pio_gpio_init(pio, BUS_PIN_DATA_BASE + i);
    gpio_set_pulls(BUS_PIN_ADDR_BASE + i, false, false);
  }
}

void setup() {
  // put your setup code here, to run once:
  set_sys_clock_khz(126 * 1000, true);
  pinMode(LED_BUILTIN, OUTPUT);
  digitalWrite(LED_BUILTIN, LOW);

  teensy_irq_gen_setup(BUS_PIO, TEENSY_IRQ_GEN_SM);
  addr_loop_setup(BUS_PIO, ADDR_LOOP_SM);
  data_loop_setup(BUS_PIO, DATA_LOOP_SM);

  // properly we should have a line in from the Teensy which we check in loop()
  // and disable the pios and LEVEL_ENABLE if it is not asserted, but I forgot
  // in the design.  Just turn stuff on for now and we'll deal with
  // it later.
  pio_enable_sm_mask_in_sync(BUS_PIO,
    (1 << TEENSY_IRQ_GEN_SM) | (1 << ADDR_LOOP_SM)
                               | (1 << DATA_LOOP_SM));

  pinMode(BUS_PIN_LEVEL_ENABLE, OUTPUT);
  digitalWrite(BUS_PIN_LEVEL_ENABLE, HIGH);
}

uint64_t last_bus_us = 0;
uint32_t bus_event_count = 0;
int bus_toggle = 0;
int led_state = 1;

void loop() {
  
  // put your main code here, to run repeatedly:
  uint64_t now = time_us_64();

  // turn LED on and leave it on if we go a second without
  // seeing any bus events
  if (now > last_bus_us + 1000000) {
    last_bus_us = now;
    digitalWrite(LED_BUILTIN, HIGH);
    led_state = 1;
  }

  // check for a bus cycle event from the irq_gen state machine.
  // the contents don't matter, we throw it away.  We just count
  // events as we get them and toggle the LED every 500k, so it flashes
  // approximately once a second.
  if (pio_sm_get_rx_fifo_level(BUS_PIO, TEENSY_IRQ_GEN_SM)) {
    pio_sm_get_blocking(BUS_PIO, TEENSY_IRQ_GEN_SM);
    ++bus_event_count;
    last_bus_us = now;
  }

  if (bus_event_count > 500000) {
    led_state = !led_state;
    digitalWrite(LED_BUILTIN, led_state);
    bus_event_count = 0;
  }

}

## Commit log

2023-07-09 timings stable with QNEthernet
2023-07-16 working demo code
2023-10-22 add Kicad project
2023-10-22 add pdf schematic
2023-10-22 fix some ground issues
2023-10-22 Changed to use single LVC07 Shrink vias to 0.6mm Spaced vias further apart Increased zone fill
2023-10-22 move vias farther from pads
2023-10-23 Caps on bus power lines
2023-10-23 remove non-routed holes from teensy footprint
2023-10-23 part picks and cleanup
2023-10-24 Add pico reset, rotate pico to point USB up
2023-10-24 reduce board to 2.625in vertical
2023-10-29 traces wiped
2023-10-29 4 layer complete
2023-10-30 revisions, passed JLCPCB verification
2023-10-30 change Pico power from 5v to VIN
2023-10-30 missing ground trace on U5
2023-10-31 Increased via spacing
2023-11-12 draft update of pico PIO code
2023-12-30 Working v1 board and firmware
2023-12-30 Add notes to readme
2023-12-30 More readme comments
2024-01-14 reset detection
2024-01-15 fix reset detect
2024-01-15 bus uncompressed, IIgs version define
2024-01-15 no bus compression, IIgs define
2024-01-20 adjust timing for Teensy 600MHz clock
2024-01-25 set IIgs mode
2024-01-27 v2 board attempt
2024-01-28 v2 board first draft done
2024-01-29 fixes
2024-01-29 pcb debugging, first draft of PIO
2024-01-31 checkpoint before lvc573 rework
2024-02-03 board ordered
2024-02-04 teensy code WIP
2024-02-24 v2 semi-working
2024-03-09 V2 board working for unidirectional bus snooping
2024-03-09 Disable serial
2024-03-18 boot injection with VBL
2024-03-24 fake boot for VBL detect in slot 7, fake vidhd in slot 2
2024-03-24 make fake vidhd slot choice configurable
2024-03-29 change reset detect to use RES
2024-05-23 bus-to-cable card
2024-06-10 checkin board draft
2024-07-14 checkin of v4/v5
2024-07-14 alchitry checkin
2024-07-15 v5 first draftw
2024-07-24 wip, reworking
2024-07-30 final v5.3
2024-07-31 v5 point
2024-08-01 v5 board order
2024-11-17 v5.1 Kicad design, v5.1 Alchitry design
2024-11-23 Mockingboard support
2024-11-24 missed add via6522
2024-11-24 data_manager add
2025-01-11 dir move
2025-01-11 initial checkin
2025-01-12 Working 5_1_1
2025-01-22 checkin before breaking stuff with v5_1_2
2025-02-23 archiving v5_1_2 before starting v5_1_3
2025-04-12 yarz testing project
2025-04-12 add ip_user_files
2025-04-12 add dcp
2025-04-12 working ft tx implementation
2025-04-13 blinky
2025-05-25 working register interface
2025-05-25 NSC time set support
2025-05-25 missing file
2025-06-02 Add board v5_2
2025-07-24 state before Init Hello
